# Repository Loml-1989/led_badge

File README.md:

# LED Badge Project
Welcome to the LED Badge project! This is an open-source, wearable LED badge build using ESP32 as microcontroller and ws2812b LEDs.
This repo contains the full kicad schematic and PCB files.
## Features
- **Microcontroller**: Powered by the smol Seeed Studio XIAO ESP32-C5. It provides wifi and bluetooth capabilities, allowing for wireless animation control, and web interfaces.
- **Display**: A matrix of ws2812b (2020) LEDs.
- **User Input**: Integrated tactile push buttons for physical interactions such as mode switching, and brightness adjustments.
- **Form Factor**: Designed as a minimal 2 layer PCB for wearing as badge.
## Hardware Specifications
- **MCU**: XIAO ESP32-C5 SMD
- **LEDs**: ws2812b-2020
- **Passives**: Standard 0805 imperial (2012 metric) SMD resistors and capacitors
- **Switches**: 6mm tactile push buttons
## Manufacturing the PCB
Download the gerber file and use your preferred manufacturer. 
## Firmware (Coming Soon)
I didn't make it yet.
## License  
This hardware design is open-source. Feel free to fork, modify, and build upon the design for your own custom wearable badges!

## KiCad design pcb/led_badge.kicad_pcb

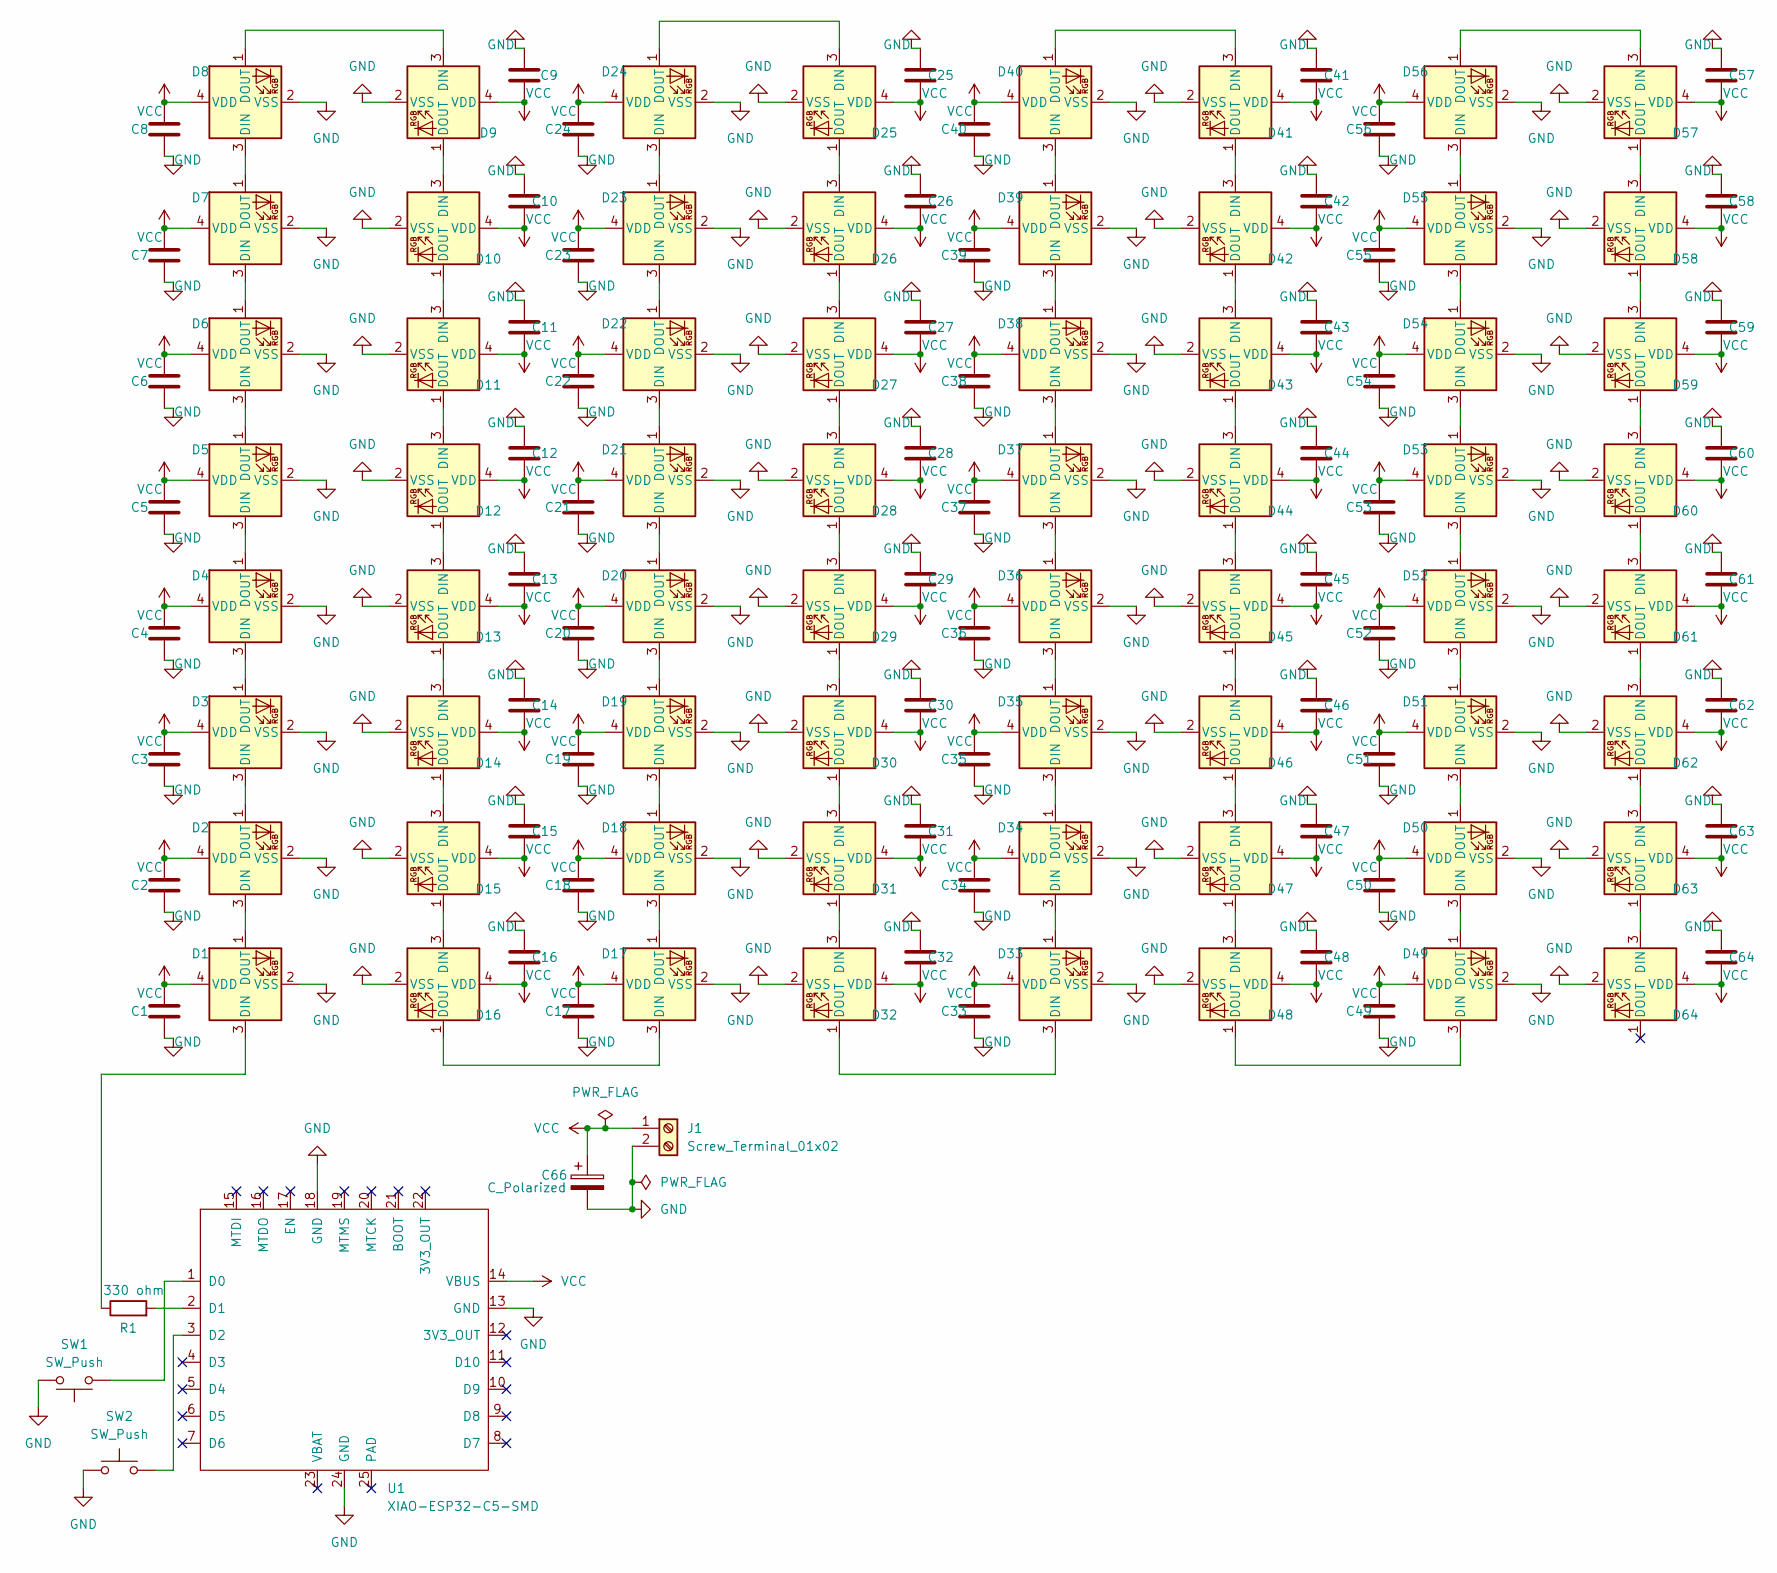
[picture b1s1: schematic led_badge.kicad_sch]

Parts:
C1, C2, C3, C4, C5, C6, C7, C8, C9, C10, C11, C12, C13, C14, C15, C16, C17, C18, C19, C20, C21, C22, C23, C24, C25, C26, C27, C28, C29, C30, C31, C32, C33, C34, C35, C36, C37, C38, C39, C40, C41, C42, C43, C44, C45, C46, C47, C48, C49, C50, C51, C52, C53, C54, C55, C56, C57, C58, C59, C60, C61, C62, C63, C64: 100nF; C_0805_2012Metric
C66: C_Polarized; CP_Radial_D10.0mm_P5.00mm
D1, D2, D3, D4, D5, D6, D7, D8, D9, D10, D11, D12, D13, D14, D15, D16, D17, D18, D19, D20, D21, D22, D23, D24, D25, D26, D27, D28, D29, D30, D31, D32, D33, D34, D35, D36, D37, D38, D39, D40, D41, D42, D43, D44, D45, D46, D47, D48, D49, D50, D51, D52, D53, D54, D55, D56, D57, D58, D59, D60, D61, D62, D63, D64: WS2812B-2020; LED_WS2812B-2020_PLCC4_2.0x2.0mm
J1: Screw_Terminal_01x02; WSON-8-1EP_6x5mm_P1.27mm_EP3.4x4mm
R1: 330 ohm; R_0805_2012Metric
SW1, SW2: SW_Push; SW_PUSH_6mm
U1: XIAO-ESP32-C5-SMD

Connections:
GND: C1.2, C2.2, C3.2, C4.2, C5.2, C6.2, C7.2, C8.2, C9.2, C10.2, C11.2, C12.2, C13.2, C14.2, C15.2, C16.2, C17.2, C18.2, C19.2, C20.2, C21.2, C22.2, C23.2, C24.2, C25.2, C26.2, C27.2, C28.2, C29.2, C30.2, C31.2, C32.2, C33.2, C34.2, C35.2, C36.2, C37.2, C38.2, C39.2, C40.2, C41.2, C42.2, C43.2, C44.2, C45.2, C46.2, C47.2, C48.2, C49.2, C50.2, C51.2, C52.2, C53.2, C54.2, C55.2, C56.2, C57.2, C58.2, C59.2, C60.2, C61.2, C62.2, C63.2, C64.2, C66.2, D1.2 (VSS), D2.2 (VSS), D3.2 (VSS), D4.2 (VSS), D5.2 (VSS), D6.2 (VSS), D7.2 (VSS), D8.2 (VSS), D9.2 (VSS), D10.2 (VSS), D11.2 (VSS), D12.2 (VSS), D13.2 (VSS), D14.2 (VSS), D15.2 (VSS), D16.2 (VSS), D17.2 (VSS), D18.2 (VSS), D19.2 (VSS), D20.2 (VSS), D21.2 (VSS), D22.2 (VSS), D23.2 (VSS), D24.2 (VSS), D25.2 (VSS), D26.2 (VSS), D27.2 (VSS), D28.2 (VSS), D29.2 (VSS), D30.2 (VSS), D31.2 (VSS), D32.2 (VSS), D33.2 (VSS), D34.2 (VSS), D35.2 (VSS), D36.2 (VSS), D37.2 (VSS), D38.2 (VSS), D39.2 (VSS), D40.2 (VSS), D41.2 (VSS), D42.2 (VSS), D43.2 (VSS), D44.2 (VSS), D45.2 (VSS), D46.2 (VSS), D47.2 (VSS), D48.2 (VSS), D49.2 (VSS), D50.2 (VSS), D51.2 (VSS), D52.2 (VSS), D53.2 (VSS), D54.2 (VSS), D55.2 (VSS), D56.2 (VSS), D57.2 (VSS), D58.2 (VSS), D59.2 (VSS), D60.2 (VSS), D61.2 (VSS), D62.2 (VSS), D63.2 (VSS), D64.2 (VSS), J1.2, SW1.2, SW2.1, U1.13 (GND), U1.18 (GND), U1.24 (GND)
unnamed: D1.3 (DIN), R1.1
unnamed: D1.1 (DOUT), D2.3 (DIN)
unnamed: D2.1 (DOUT), D3.3 (DIN)
unnamed: D3.1 (DOUT), D4.3 (DIN)
unnamed: D4.1 (DOUT), D5.3 (DIN)
unnamed: D5.1 (DOUT), D6.3 (DIN)
unnamed: D6.1 (DOUT), D7.3 (DIN)
unnamed: D7.1 (DOUT), D8.3 (DIN)
unnamed: D8.1 (DOUT), D9.3 (DIN)
unnamed: D9.1 (DOUT), D10.3 (DIN)
unnamed: D10.1 (DOUT), D11.3 (DIN)
unnamed: D11.1 (DOUT), D12.3 (DIN)
unnamed: D12.1 (DOUT), D13.3 (DIN)
unnamed: D13.1 (DOUT), D14.3 (DIN)
unnamed: D14.1 (DOUT), D15.3 (DIN)
unnamed: D15.1 (DOUT), D16.3 (DIN)
unnamed: D16.1 (DOUT), D17.3 (DIN)
unnamed: D17.1 (DOUT), D18.3 (DIN)
unnamed: D18.1 (DOUT), D19.3 (DIN)
unnamed: D19.1 (DOUT), D20.3 (DIN)
unnamed: D20.1 (DOUT), D21.3 (DIN)
unnamed: D21.1 (DOUT), D22.3 (DIN)
unnamed: D22.1 (DOUT), D23.3 (DIN)
unnamed: D23.1 (DOUT), D24.3 (DIN)
unnamed: D24.1 (DOUT), D25.3 (DIN)
unnamed: D25.1 (DOUT), D26.3 (DIN)
unnamed: D26.1 (DOUT), D27.3 (DIN)
unnamed: D27.1 (DOUT), D28.3 (DIN)
unnamed: D28.1 (DOUT), D29.3 (DIN)
unnamed: D29.1 (DOUT), D30.3 (DIN)
unnamed: D30.1 (DOUT), D31.3 (DIN)
unnamed: D31.1 (DOUT), D32.3 (DIN)
unnamed: D32.1 (DOUT), D33.3 (DIN)
unnamed: D33.1 (DOUT), D34.3 (DIN)
unnamed: D34.1 (DOUT), D35.3 (DIN)
unnamed: D35.1 (DOUT), D36.3 (DIN)
unnamed: D36.1 (DOUT), D37.3 (DIN)
unnamed: D37.1 (DOUT), D38.3 (DIN)
unnamed: D38.1 (DOUT), D39.3 (DIN)
unnamed: D39.1 (DOUT), D40.3 (DIN)
unnamed: D40.1 (DOUT), D41.3 (DIN)
unnamed: D41.1 (DOUT), D42.3 (DIN)
unnamed: D42.1 (DOUT), D43.3 (DIN)
unnamed: D43.1 (DOUT), D44.3 (DIN)
unnamed: D44.1 (DOUT), D45.3 (DIN)
unnamed: D45.1 (DOUT), D46.3 (DIN)
unnamed: D46.1 (DOUT), D47.3 (DIN)
unnamed: D47.1 (DOUT), D48.3 (DIN)
unnamed: D48.1 (DOUT), D49.3 (DIN)
unnamed: D49.1 (DOUT), D50.3 (DIN)
unnamed: D50.1 (DOUT), D51.3 (DIN)
unnamed: D51.1 (DOUT), D52.3 (DIN)
unnamed: D52.1 (DOUT), D53.3 (DIN)
unnamed: D53.1 (DOUT), D54.3 (DIN)
unnamed: D54.1 (DOUT), D55.3 (DIN)
unnamed: D55.1 (DOUT), D56.3 (DIN)
unnamed: D56.1 (DOUT), D57.3 (DIN)
unnamed: D57.1 (DOUT), D58.3 (DIN)
unnamed: D58.1 (DOUT), D59.3 (DIN)
unnamed: D59.1 (DOUT), D60.3 (DIN)
unnamed: D60.1 (DOUT), D61.3 (DIN)
unnamed: D61.1 (DOUT), D62.3 (DIN)
unnamed: D62.1 (DOUT), D63.3 (DIN)
unnamed: D63.1 (DOUT), D64.3 (DIN)
unnamed: SW1.1, U1.1 (D0)
unnamed: R1.2, U1.2 (D1)
unnamed: SW2.2, U1.3 (D2)
VCC: C1.1, C2.1, C3.1, C4.1, C5.1, C6.1, C7.1, C8.1, C9.1, C10.1, C11.1, C12.1, C13.1, C14.1, C15.1, C16.1, C17.1, C18.1, C19.1, C20.1, C21.1, C22.1, C23.1, C24.1, C25.1, C26.1, C27.1, C28.1, C29.1, C30.1, C31.1, C32.1, C33.1, C34.1, C35.1, C36.1, C37.1, C38.1, C39.1, C40.1, C41.1, C42.1, C43.1, C44.1, C45.1, C46.1, C47.1, C48.1, C49.1, C50.1, C51.1, C52.1, C53.1, C54.1, C55.1, C56.1, C57.1, C58.1, C59.1, C60.1, C61.1, C62.1, C63.1, C64.1, C66.1, D1.4 (VDD), D2.4 (VDD), D3.4 (VDD), D4.4 (VDD), D5.4 (VDD), D6.4 (VDD), D7.4 (VDD), D8.4 (VDD), D9.4 (VDD), D10.4 (VDD), D11.4 (VDD), D12.4 (VDD), D13.4 (VDD), D14.4 (VDD), D15.4 (VDD), D16.4 (VDD), D17.4 (VDD), D18.4 (VDD), D19.4 (VDD), D20.4 (VDD), D21.4 (VDD), D22.4 (VDD), D23.4 (VDD), D24.4 (VDD), D25.4 (VDD), D26.4 (VDD), D27.4 (VDD), D28.4 (VDD), D29.4 (VDD), D30.4 (VDD), D31.4 (VDD), D32.4 (VDD), D33.4 (VDD), D34.4 (VDD), D35.4 (VDD), D36.4 (VDD), D37.4 (VDD), D38.4 (VDD), D39.4 (VDD), D40.4 (VDD), D41.4 (VDD), D42.4 (VDD), D43.4 (VDD), D44.4 (VDD), D45.4 (VDD), D46.4 (VDD), D47.4 (VDD), D48.4 (VDD), D49.4 (VDD), D50.4 (VDD), D51.4 (VDD), D52.4 (VDD), D53.4 (VDD), D54.4 (VDD), D55.4 (VDD), D56.4 (VDD), D57.4 (VDD), D58.4 (VDD), D59.4 (VDD), D60.4 (VDD), D61.4 (VDD), D62.4 (VDD), D63.4 (VDD), D64.4 (VDD), J1.1, U1.14 (VBUS)

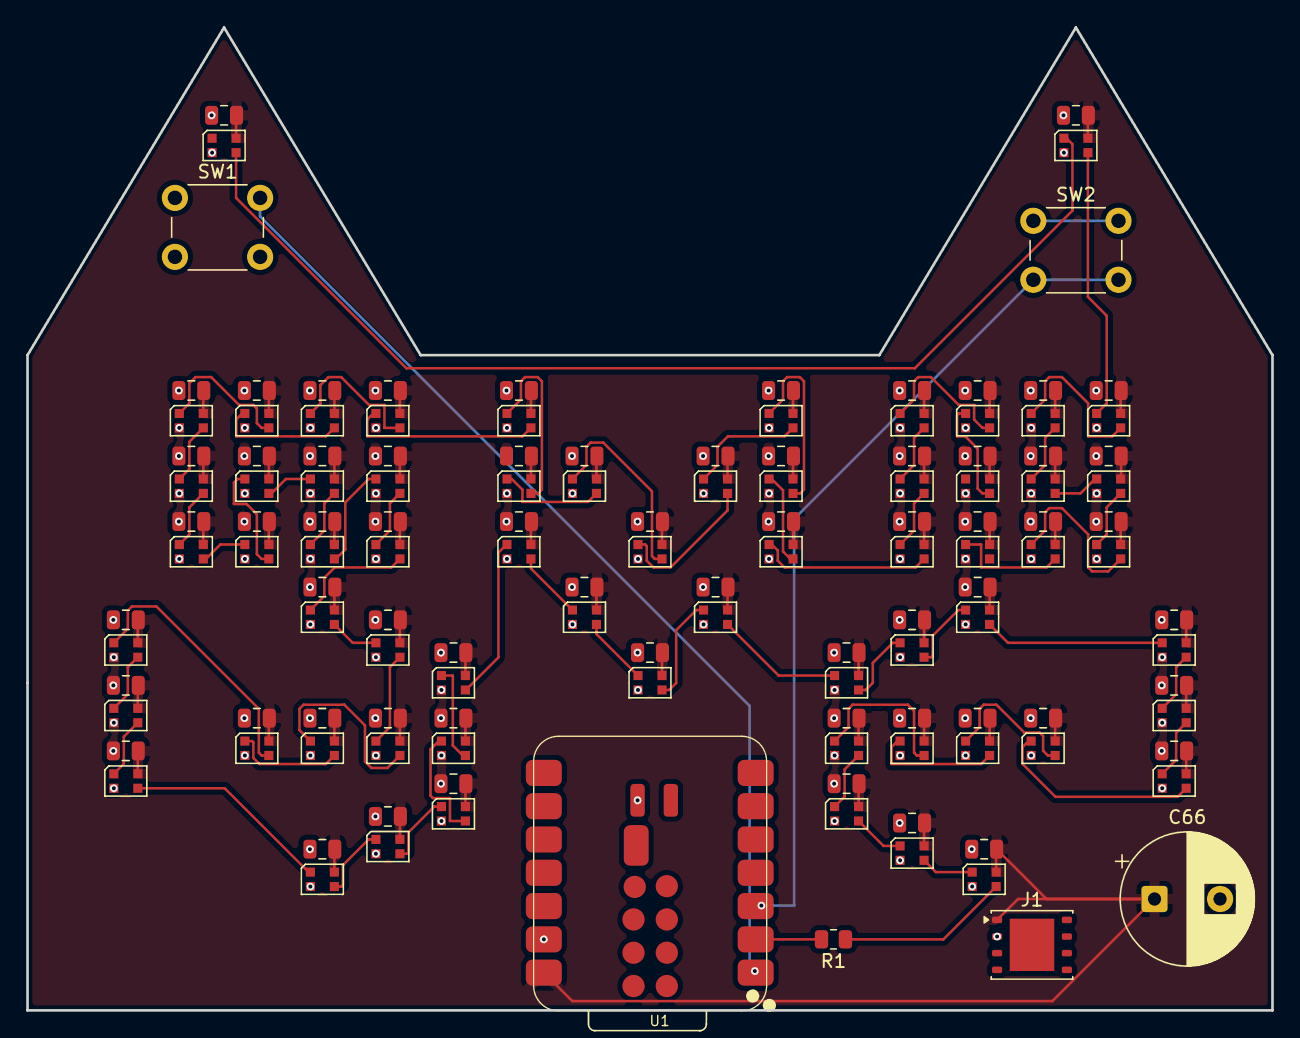
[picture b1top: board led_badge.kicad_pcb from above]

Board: 2 copper layers, 95.0 x 75.0 mm, 134 parts (0 on the bottom side), 69 nets.

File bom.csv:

Id;Designator;Footprint;Quantity;Designation;Price
1;C1, C2, C3, C4, C5, C6, C7, C8, C9, C10, C11, C12, C13, C14, C15, C16, C17, C18, C19, C20, C21, C22, C23, C24, C25, C26, C27, C28, C29, C30, C31, C32, C33, C34, C35, C36, C37, C38, C39, C40, C41, C42, C43, C44, C45, C46, C47, C48, C49, C50, C51, C52, C53, C54, C55, C56, C57, C58, C59, C60, C61, C62, C63, C64;C_0805_2012Metric;64;100nF;$1.00
2;C66;CP_Radial_D10.0mm_P5.00mm;1;C_Polarized;$1.00
3;D1, D2, D3, D4, D5, D6, D7, D8, D9, D10, D11, D12, D13, D14, D15, D16, D17, D18, D19, D20, D21, D22, D23, D24, D25, D26, D27, D28, D29, D30, D31, D32, D33, D34, D35, D36, D37, D38, D39, D40, D41, D42, D43, D44, D45, D46, D47, D48, D49, D50, D51, D52, D53, D54, D55, D56, D57, D58, D59, D60, D61, D62, D63, D64;LED_WS2812B-2020_PLCC4_2.0x2.0mm;64;WS2812B-2020;$8.00
4;J1;WSON-8-1EP_6x5mm_P1.27mm_EP3.4x4mm;1;Screw_Terminal_01x02;
5;R1;R_0805_2012Metric;1;330 ohm;$1.00
6;SW1, SW2;SW_PUSH_6mm;2;SW_Push;$1.00
7;U1;XIAO-ESP32-C5-SMD;1;XIAO-ESP32-C5-SMD;$9.50
